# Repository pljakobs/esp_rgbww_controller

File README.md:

View this project on [CADLAB.io](https://cadlab.io/project/1422). 

# ESP8266 WiFi RGBWW LED Dimmer v1.5
Custom Hardware board for controlling 5 Led Channels via PWM (RGB + Warm/Cold White). It is designed for max current ~4.5A per Channel.

# Changelog

* 1.5 (31.01.2017)
  * DCDC wandler has been remeasured and provided for through hole mounting on pin headers
  * Jumper introduced for allowing for external 3,3V connections
  * measurements have been changed to 53mm*47mm with mounting holes tailored towards "Strapubox CO 4" casing
  * C1 has been replaced with a smaller form factor

* 1.3 (20.02.2016)
  * added another tact switch which can be used during boot to reset settings
  * silksceen naming updated 

* 1.2 (16.02.2016)
  * improved the layout for better EMV
  * added buffer capacitor for dc converter
  * added filter capacitor close to ESP8266
  
* 1.1 (01.02.2016)
  * connected ADC 
  * some layout improvements

# Parts
- 1x ESP8266, ESP-12 format
- 1x XM1584 Power converter (set to 3.3v!)
- 5x IRLZ44N Mosfet (logic level gate threshold)
- 11x 10k resistors, 0805 (R1 - R11)
- 1x 1k resistors, 0805 (R12)
- 1x 330 µF Elko RM 2.5 mm (C1) 
- 1x 100 µF Elko RM 2.5 mm (C3)
- 1x 100 nF capacitor 0805(C2)
- 3x 5,08mm 2pin terminal block
- 1x 5,08mm 3pin terminal block
- 1x 2,54mm 4pin header
- 2x Micro SMD Tact Switch 2 pin 3*6*2.5 mm (optional)

# Assembly
Assembly of the PCB Board is straight forward, solder all parts to the PCB.

__Caution :__ before soldering the esp module to the PCB, set the output voltage of XM1584 converter  to 3.3v

### Recommended steps
- Start with soldering the smd resistors
- __Ensure the output voltage of XM1584 converter is 3.3v before continuing__. 
- Solder the XM1584 Power Board 
- Solder ESP8266 Module 
- Optional: solder SMD Tact Switch
- Solder Elkos
- Solder Terminal Blocks, 4pin header 
- Solder FETs

# Firmware
Firmware is still work in progress.

Latest can be found here:
https://github.com/patrickjahns/esp_rgbww_controller_fw

# Modifying
The schematic and board files are compatible with eagle 7.2+

## Ideas
Here are some ideas for future revisions
- see if we can clear some GPIOs and provide them via PIN Header for other enhancements (i.e. IR / Rotary Controller) 
- change layout for VCC/GND to be on the left side
- ~~connect ADC to detect power failure~~ 

# Resources
* [ESP RGB Project](https://github.com/RiRomain/esp-dimmer-hardware)
* [H801 Wifi Controller Hack](http://chaozlabs.blogspot.de/2015/08/esp8266-in-wild-wifi-led-controller-hack.html)

# Thread in Fhem Forum
* [Entwicklung/Sammelbestellung RGBWW Wifi Led Controller](https://forum.fhem.de/index.php/topic,48918.msg)

# Credits
Thanks to RiRomain for his excellent documentated [ESP RGB Project](https://github.com/RiRomain/esp-dimmer-hardware)

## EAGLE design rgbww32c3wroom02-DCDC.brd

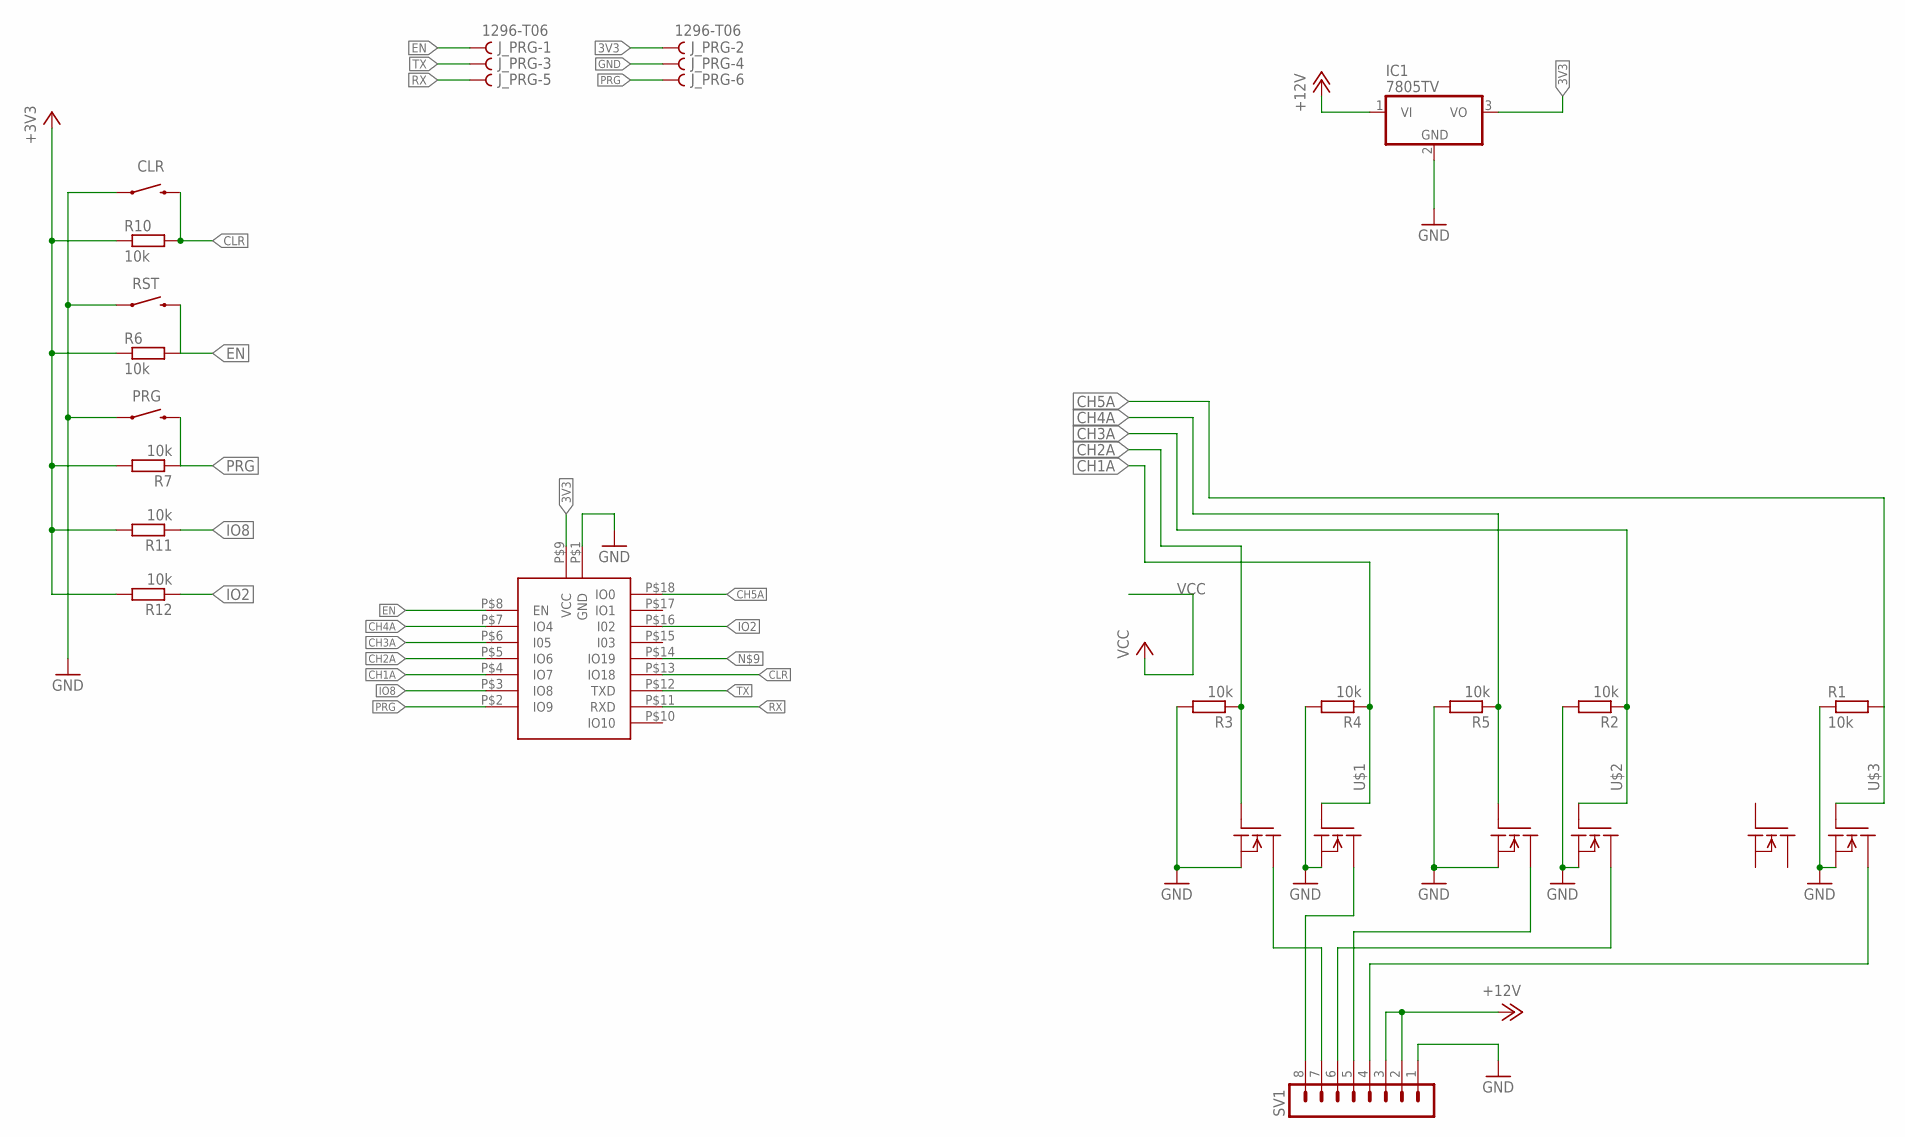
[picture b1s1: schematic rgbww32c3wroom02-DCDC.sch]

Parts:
CLR: SWITCH-MOMENTARY-2SMD-1101NE; TACTILE-SWITCH-1101NE
IC1: 7805TV; TO220V
J_PRG: 1296-T06; 06
PRG: SWITCH-MOMENTARY-2SMD-1101NE; TACTILE-SWITCH-1101NE
R1, R2, R3, R4, R5, R6, R7, R10, R11, R12: 10k; R0805
RST: SWITCH-MOMENTARY-2SMD-1101NE; TACTILE-SWITCH-1101NE
SV1: MA08-1
U$1, U$2, U$3: AOD4806; SO08
U$5: ESP32C3WROOM02; SMD

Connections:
3V3: IC1.3 (VO), J_PRG.2, R6.1, R7.2, R10.1, R11.2, R12.2, U$5.P$9 (VCC)
12V: IC1.1 (VI), SV1.2, SV1.3
CH1: SV1.8, U$1.5 (D), U$1.6 (D)
CH1A: R4.1, U$1.4 (G), U$5.P$4 (IO7)
CH2: SV1.7, U$1.7 (D1), U$1.8 (D1)
CH2A: R3.1, U$1.2 (G1), U$5.P$5 (IO6)
CH3: SV1.6, U$2.5 (D), U$2.6 (D)
CH3A: R2.1, U$2.4 (G), U$5.P$6 (I05)
CH4: SV1.5, U$2.7 (D1), U$2.8 (D1)
CH4A: R5.1, U$2.2 (G1), U$5.P$7 (IO4)
CH5: SV1.4, U$3.5 (D), U$3.6 (D)
CH5A: R1.2, U$3.4 (G), U$5.P$18 (IO0)
CLR: CLR.2, R10.2, U$5.P$13 (IO18)
EN: J_PRG.1, R6.2, RST.2, U$5.P$8 (EN)
GND: CLR.1, IC1.2 (GND), J_PRG.4, PRG.1, R1.1, R2.2, R3.2, R4.2, R5.2, RST.1, SV1.1, U$1.1 (S1), U$1.3 (S), U$2.1 (S1), U$2.3 (S), U$3.3 (S), U$5.P$1 (GND)
IO2: R12.1, U$5.P$16 (I02)
IO8: R11.1, U$5.P$3 (IO8)
PRG: J_PRG.6, PRG.2, R7.1, U$5.P$2 (IO9)
RX: J_PRG.5, U$5.P$11 (RXD)
TX: J_PRG.3, U$5.P$12 (TXD)

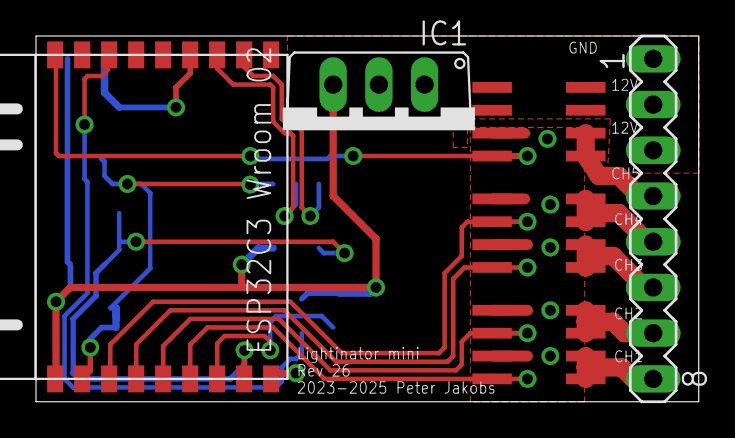
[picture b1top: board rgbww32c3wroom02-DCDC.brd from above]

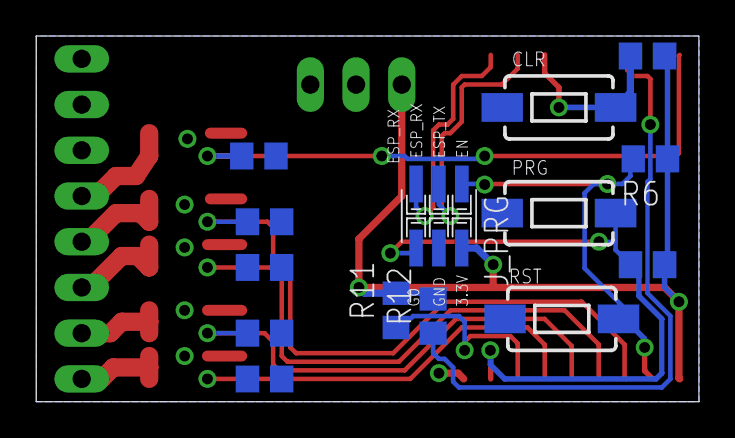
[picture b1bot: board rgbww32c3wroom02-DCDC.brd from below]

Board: 2 copper layers, 36.8 x 20.3 mm, 20 parts (14 on the bottom side), 20 nets.

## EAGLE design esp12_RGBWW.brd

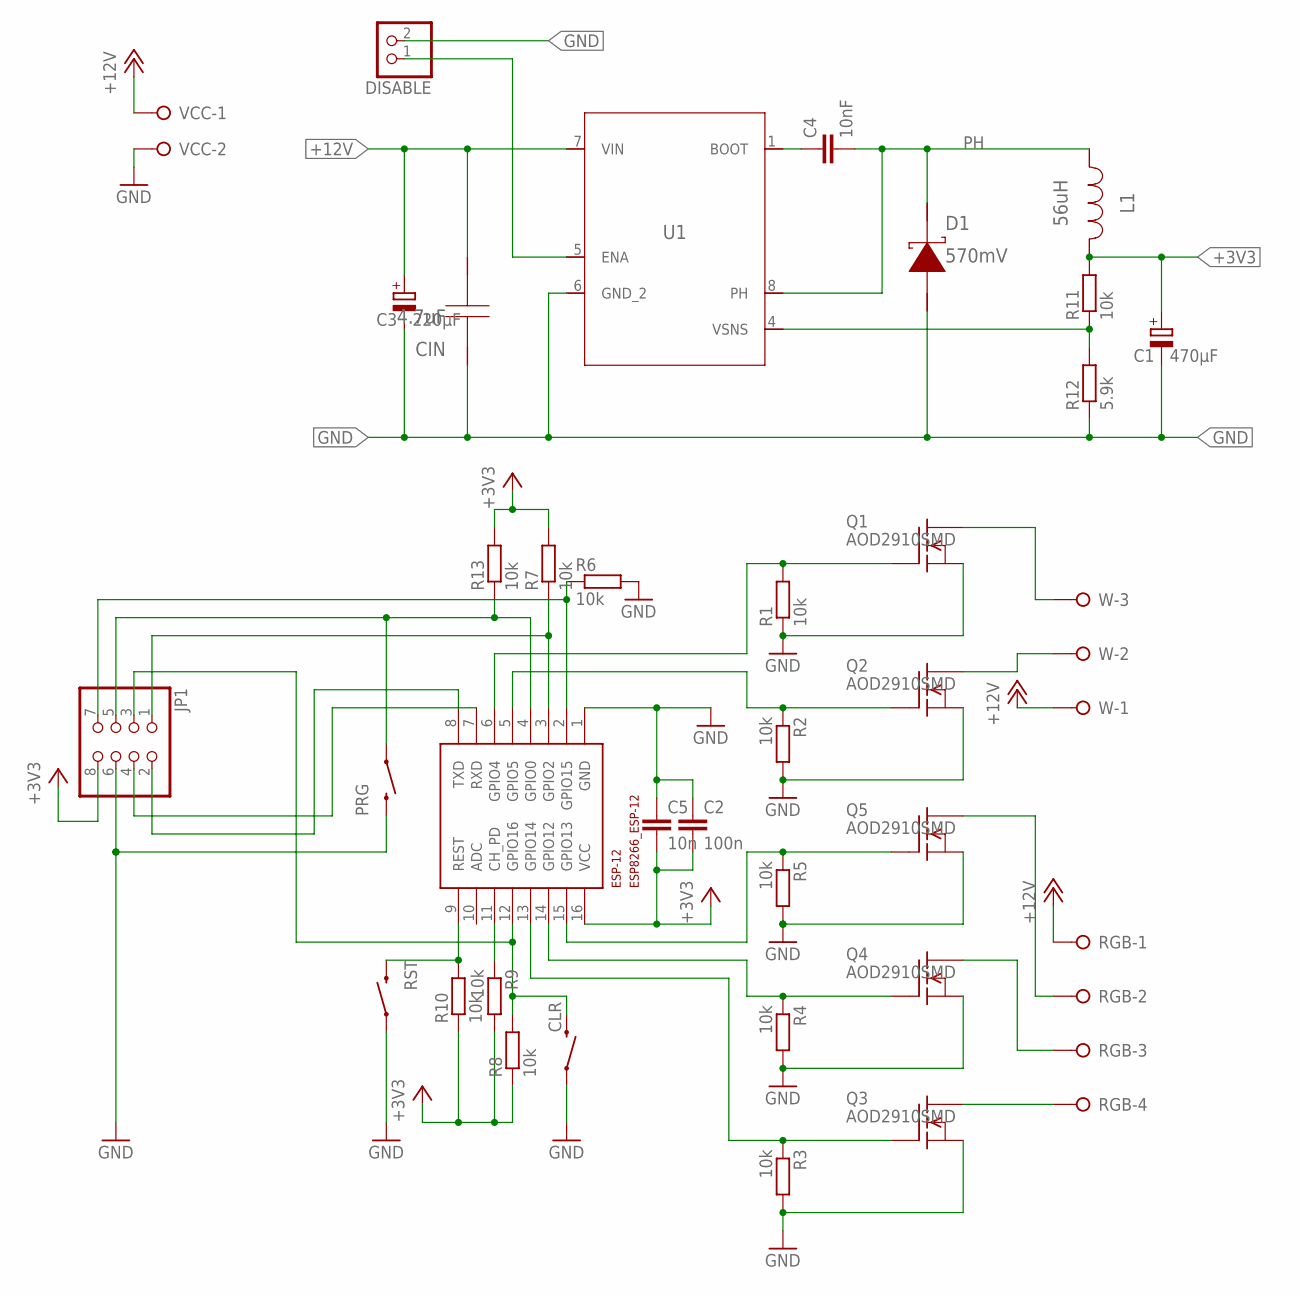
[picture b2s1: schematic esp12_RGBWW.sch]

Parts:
C1: 470µF; E2,5-7
C2: 100n; C0805
C3: 220µF; E2,5-7
C4: 10nF; C0805
C5: 10n; C0805
CIN: 4.7uF; 1206
CLR: SWITCH-MOMENTARY-2SMD-1101NE; TACTILE-SWITCH-1101NE
D1: 570mV; SMA
DISABLE: PINHD-1X2; 1X02
ESP-12: ESP8266_ESP-12; ESP8266-ESP12
JP1: PINHD-2X4; 2X04
L1: 56uH; IND_NPI75C
PRG: SWITCH-MOMENTARY-2SMD-1101NE; TACTILE-SWITCH-1101NE
Q1, Q2, Q3, Q4, Q5: AOD2910SMD; DPAK-3
R1, R2, R3, R4, R5, R6, R7, R8, R9, R10, R11, R13: 10k; R0805
R12: 5.9k; R0805
RGB: W237-04P; W237-4P
RST: SWITCH-MOMENTARY-2SMD-1101NE; TACTILE-SWITCH-1101NE
U1: TPS5410DR; M08A
VCC: W237-02P; W237-132
W: W237-03P; W237-133

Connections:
+3V3: C1.+, C2.2, C5.2, ESP-12.16 (VCC), JP1.8, L1.1, R7.2, R8.1, R9.2, R10.1, R11.2, R13.2
+12V: C3.+, CIN.2, RGB.1, U1.7 (VIN), VCC.1, W.1
B: Q3.4 (D), RGB.4
BOOT: C4.1, U1.1 (BOOT)
CH_PD: ESP-12.11 (CH_PD), R9.1
CLR_S: CLR.2, ESP-12.12 (GPIO16), JP1.3, R8.2
CW: Q2.4 (D), W.2
ENA: DISABLE.1, U1.5 (ENA)
G: Q4.4 (D), RGB.3
G2: ESP-12.3 (GPIO2), JP1.1, R7.1
G15: ESP-12.2 (GPIO15), JP1.7, R6.1
GND: C1.-, C2.1, C3.-, C5.1, CIN.1, CLR.1, D1.2 (A), DISABLE.2, ESP-12.1 (GND), JP1.6, PRG.2, Q1.3 (S), Q2.3 (S), Q3.3 (S), Q4.3 (S), Q5.3 (S), R1.1, R2.2, R3.2, R4.2, R5.2, R6.2, R12.1, RST.1, U1.6 (GND_2), VCC.2
PH: C4.2, D1.1 (K), L1.2, U1.8 (PH)
PRG_S: ESP-12.4 (GPIO0), JP1.5, PRG.1, R13.1
R: Q5.4 (D), RGB.2
RGB-B: ESP-12.13 (GPIO14), Q3.1 (G), R3.1
RGB-CW: ESP-12.5 (GPIO5), Q2.1 (G), R2.1
RGB-G: ESP-12.14 (GPIO12), Q4.1 (G), R4.1
RGB-R: ESP-12.15 (GPIO13), Q5.1 (G), R5.1
RGB-WW: ESP-12.6 (GPIO4), Q1.1 (G), R1.2
RST_S: ESP-12.9 (REST), R10.2, RST.2
RXD: ESP-12.7 (RXD), JP1.4
SENS: R11.1, R12.2, U1.4 (VSNS)
TXD: ESP-12.8 (TXD), JP1.2
WW: Q1.4 (D), W.3

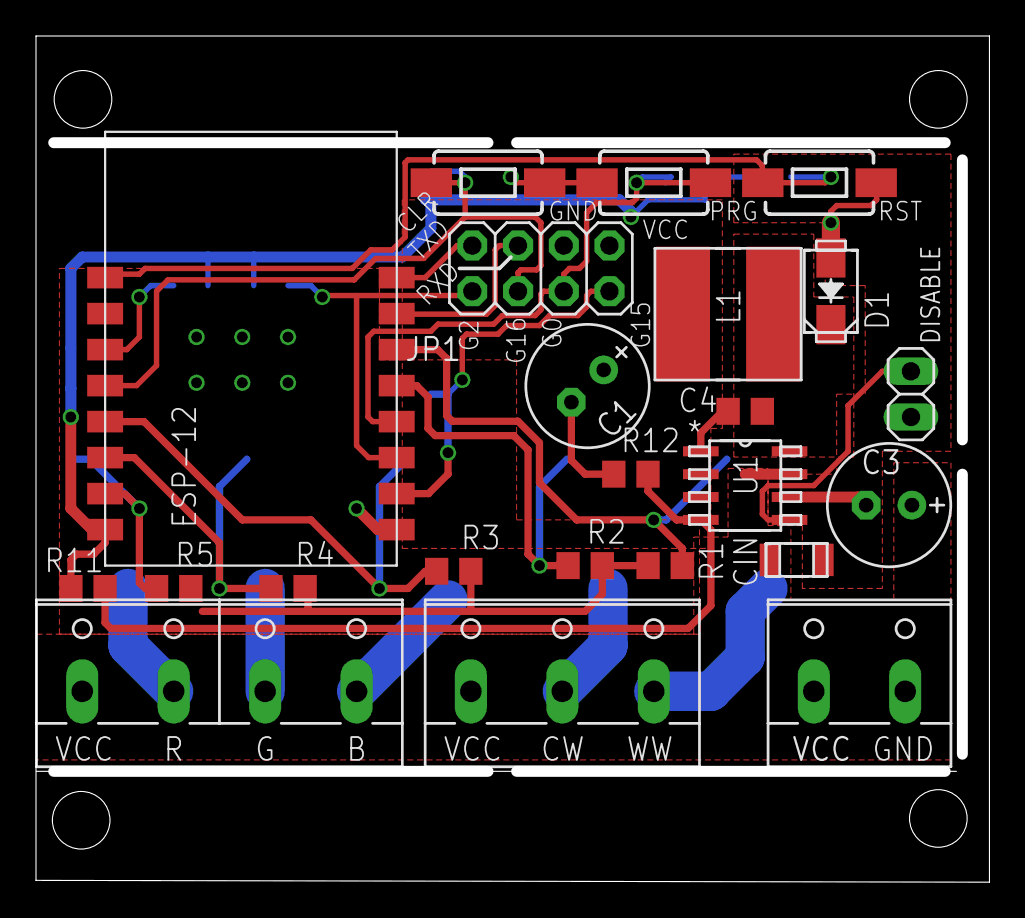
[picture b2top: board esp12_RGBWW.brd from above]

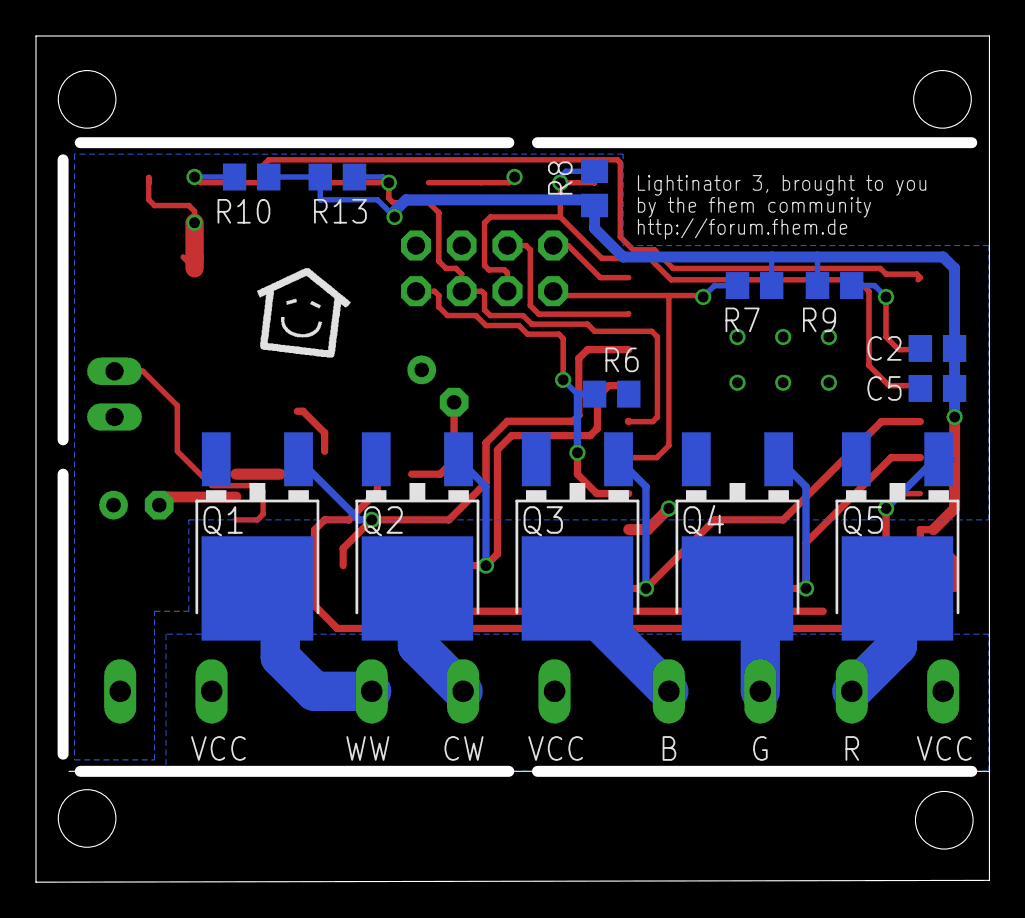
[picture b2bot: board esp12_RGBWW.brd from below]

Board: 2 copper layers, 52.4 x 46.4 mm, 37 parts (14 on the bottom side), 25 nets.

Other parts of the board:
U$1: LOGO

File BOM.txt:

C1       1000uF 6.3V    E2,5-7
C2       100n           C0805
C3       240uF 35V      E2,5-7
C4       10nF           C0805 
CIN      4.7uF          1206   
D1       PMEG6010CEH115 SOD-123F
ESP-12   ESP8266_ESP-12 ESP8266-ESP12
L1       56uH           IND_NPI75C
PROG     pin header     MA03-1
Q1-Q5    AOD2910SMD     DPAK-3
R1-R11   10k            R0805
R12      5.9k           R0805
R13      10k            R0805
RST      Switch         TACTILE-SWITCH-1101NE
PRG      Switch         TACTILE-SWITCH-1101NE
CLR      Switch         TACTILE-SWITCH-1101NE
U1       TPS5410DR      M08A 
VCC      Schraubklemme  W237-132
W        Schraubklemme  W237-133
RGB      Schraubklemme  W237-4P

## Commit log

2017-10-04 new, smaller board
    new design, integrated DCDC converter, new, smaller MOSFETs, smaller overal board, additional PRG button, mostly optimized for SMD manufacturing but still hand solderable
2017-11-19 minor placement changes
2017-11-19 another reduction in size
    replaced most of the power supply parts, shaved off another 3mm
2018-03-01 updated silk screen
    some minor changes, mostly cleaned up silk screen
2018-03-01 added BOM
    BOM
2018-04-07 added enable function
    I added a pin header to short the TPS5410's ENABLE pin to GND, thus switching off the DC/DC converter, effectively turning the controller completely off.
    The controller should function normally, when this is left open. Including a switch that connects those two pins is a way of switching the controller off without disconnecting the 12V supply. Whateve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
2018-04-11 some power supply improvements
    added a snubber network to PH (140MHz) plus a 10nF cap on the +3V3 line
    Added low impedance floodfills for +3V3 and PH where applicable
    switched the location of the RST and PRG switches since it seems easier to have the RST on the outside
2018-04-14 more board improvements
    - floodfills for VCC, PH and top layer +3V3 nods
    - RC snubber for PH node
    - additional 10nF cap close to the ESPs 3.3V
    - cleaned up the GND layer a bit
2018-05-05 yet more minor changes on the input side
    removed the snubber pads
    created a lower impedance GND path
    swiched RXD and TXD for some more elegant routing and better fit with the usual USB/UART connectors (straight cable now switches RX/TX)
    minor silkscreen corrections for better legibility
2018-05-12 updated Gerber Files and Pictures
    exported Gerber Files, shot a few new pictures of the board.
    Unlike the Beta Boards, this version does not have pads for an R/C snubber as I don't think it will be necessary. Also, there's a larger GND area covering the top layer input side of the circuit and 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
    The TXD and RXD pins have switched places, it was easier to route them like that and also, their location now crosses over with the usual USB/UART converters (straight cable run).
    On the disable jumper location, the pins have also switched places, disable is now on the top, pointing away from C3
2018-05-12 added two dimension measurements
2018-05-12 cosmetical correction
    beautified the crossing of RXD and TXD
2018-09-13 minor routing changes
    updated a few minor routings (clr) and added some more copper areas (GND around DISABLE & D1)
2018-11-14 Backlink to CADLAB.io has been added.
2018-11-15 fixed a pretty embarassing error
    I had one ground trace clip one of the PWM output pads.
2018-11-21 minor change
    one of the GND traces (between R2 and R3) underneath the top ground plane was not connected - doesn't make a change in the final board since it's one copper layer anyway.
2018-12-01 added six pin connector for programming
    changed the three pin programming header to a six pin version, allowing to directly plug in one of the universal FTDI based USB to UART adaptors.
    Pinout is:
    1: GND
    2: NC
    3: NC
    4: RX
2018-12-01 created a bit more room for a sliding mount by moving the decoupling caps C2 and C5 in a bit.
2019-01-27 minor changes
    increased the size of the button text
    very minor re-route of GPIO2 to resistor
2019-02-03 updated gerber files
2019-02-04 added three accessible GPIOs
    Added header pins for GPIOS 0,2 and 16 (which are all pulled high on board).
    If using Tasmota, or if we make changes to the "native" firmware, those can be used to signal via MQTT and thus to provide "local" control
2019-02-04 minor update
    moved one signal in the schematic, no electrical change
2019-02-04 minor corrections
    mainly values to make sure the BOM is all right
2019-02-16 small changes
2019-02-27 Update esp12_RGBWW.sch
    I had added and removed a power jack.
2019-03-13 small silkscreen changes
2019-03-13 added fhem logo and reference
2019-10-06 final production version
2019-11-08 added VCC and G15 to pin header
    in the earlier design, I had omitted a VCC pin at the pin header. That could be a useful pin for folks using the board with the TAMSOTA firmware, opening up a few pins for external sensors.
    Now G0, G2, G15 and G16 are available on the header.
    When using them, you should be aware that G0, G2 and G16 are internally pulled up and G15 is pulled low. depending on the loaded firmware, changing the level of those pins (especially at boot time) m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
2025-04-18 commitintg the Lightinator mini design in Eagle format
2025-04-18 initial kicad versions
2025-04-18 project changes by opening it on linux for the first time

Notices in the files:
parts and their libraries:
SparkFun-Electromechanical: Licensing: Creative Commons ShareAlike 4.0 International - https://creativecommons.org/licenses/by-sa/4.0
SparkFun-Aesthetics: Licensing: CC v3.0 Share-Alike You are welcome to use this library for commercial purposes.
